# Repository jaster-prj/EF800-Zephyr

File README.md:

# EF800 Zephyr workspace

This repository migrates the EF800 firmware from Mbed OS to Zephyr. Builds run
inside the devcontainer so the Zephyr revision and toolchain do not depend on a
developer's host setup.

The devcontainer follows the `zephyr_gartennode_poolmodul` layout:

```text
/workspace/                         west workspace and build root
/workspace/application/             this Git repository
/workspace/application/application/ firmware applications
/workspace/zephyr/                  downloaded Zephyr checkout
```

The container is intended to be reused during development. `west update` is
not run every time a terminal is opened. Run the initialization commands once
after creating the container; later sessions can build directly.

## Reusable workspace

The development image can already contain a populated west workspace. Inspect
it before running any network operation:

```sh
/opt/venv/bin/west topdir
/opt/venv/bin/west config manifest.path
/opt/venv/bin/west config manifest.file
/opt/venv/bin/west list zephyr -f "{path} {revision} {sha}"
```

If the workspace is `/workspace`, the manifest is
`application/manifest-repo/west.yml`, and Zephyr matches the revision in
`manifest-repo/west.yml`, build directly. Do not run `west update` for normal
development sessions.

Only initialize or update a new, incomplete, or manifest-mismatched container:

```sh
if [ -d .west ]; then
  /opt/venv/bin/west config manifest.path application/manifest-repo
  /opt/venv/bin/west config manifest.file west.yml
else
  /opt/venv/bin/west init -l application/manifest-repo
fi
/opt/venv/bin/west update
/opt/venv/bin/west zephyr-export
/opt/venv/bin/python -m pip install -r zephyr/scripts/requirements.txt
```

Build the six firmware targets with:

```sh
/opt/venv/bin/west build -p always -b ef800 application/application/ef800-application -d application/build/ef800-application
/opt/venv/bin/west build -p always -b ef800 application/application/ef800-backup -d application/build/ef800-backup
/opt/venv/bin/west build -p always -b ef800 application/application/ef800-bootloader -d application/build/ef800-bootloader
/opt/venv/bin/west build -p always -b ef800_keyboard application/application/keyboard-application -d application/build/keyboard-application
/opt/venv/bin/west build -p always -b ef800_keyboard application/application/keyboard-bootloader -d application/build/keyboard-bootloader
/opt/venv/bin/west build -p always -b ef800_keyboard application/application/keyboard-updater -d application/build/keyboard-updater
bash application/scripts/verify-images.sh
```

For the temporary, read-only external-flash hardware-debug image:

```sh
/opt/venv/bin/west build -p always -b ef800 application/application/test-hwdebug -d application/build/test-hwdebug
bash application/scripts/verify-test-hwdebug-image.sh
```

This image replaces the second-level bootloader at `0x08000000` and must only
be used on a recoverable engineering target. It provides a USB CDC diagnostic
console and read-only SPI/QSPI/QPI probing with recovery boundaries; see
`docs/hardware-debug-qspi.md`.

The same commands are collected in `.devcontainer/commands.txt`.

The board definitions are currently kept in this mounted application repository
under `boards/` so the first bring-up does not require a second repository.
They can be moved into a shared Zephyr board module once the hardware has been
verified.

## Current layout

The legacy EF800 internal flash contract is retained for the first migration
increment:

```text
0x08000000 - 0x0800FFFF  second-level bootloader
0x08010000 - 0x0802FFFF  backup application
0x08030000 - 0x080FFFFF  EF800 application
```

The current Zephyr contract reserves `0x08028000..0x0802FFFF` for boot
metadata. The captured legacy `BackupApplication.bin` is 128 KiB and uses that
range, so the reservation must not be treated as unused when restoring the
legacy image. The external QSPI flash is configured as the identified
`IS25LP032D-JTLE-TR` 32-Mbit / 4-MiB device. JEDEC ID, SFDP, signal integrity,
erase geometry, and existing FAT contents still require hardware validation
before production flashing.

The connected STM32L496 engineering target was erased and verified blank during
initial recovery preparation, then later used for controlled bootloader and
EF800 Application bring-up. See `docs/stm32l496-target-snapshot.md` for the
historical option-byte values, recovery-image hashes, and erase record. See
`docs/migration-status.md` for current migration state.

See `docs/` for the migration contract and hardware assumptions.

The system architecture is documented under [`architecture/`](architecture/index.md)
using separately maintained arc42 sections, with block views and runtime
diagrams under `architecture/diagram_as_code/`.

For physical target testing with semantic virtual keyboard input, see
`docs/hardware-debug-keyboard.md`.

For the TLX-711A virtual controller and framebuffer viewer, see
`GSE/TLX-711A/README.md` and build `application/tlx-711a`.

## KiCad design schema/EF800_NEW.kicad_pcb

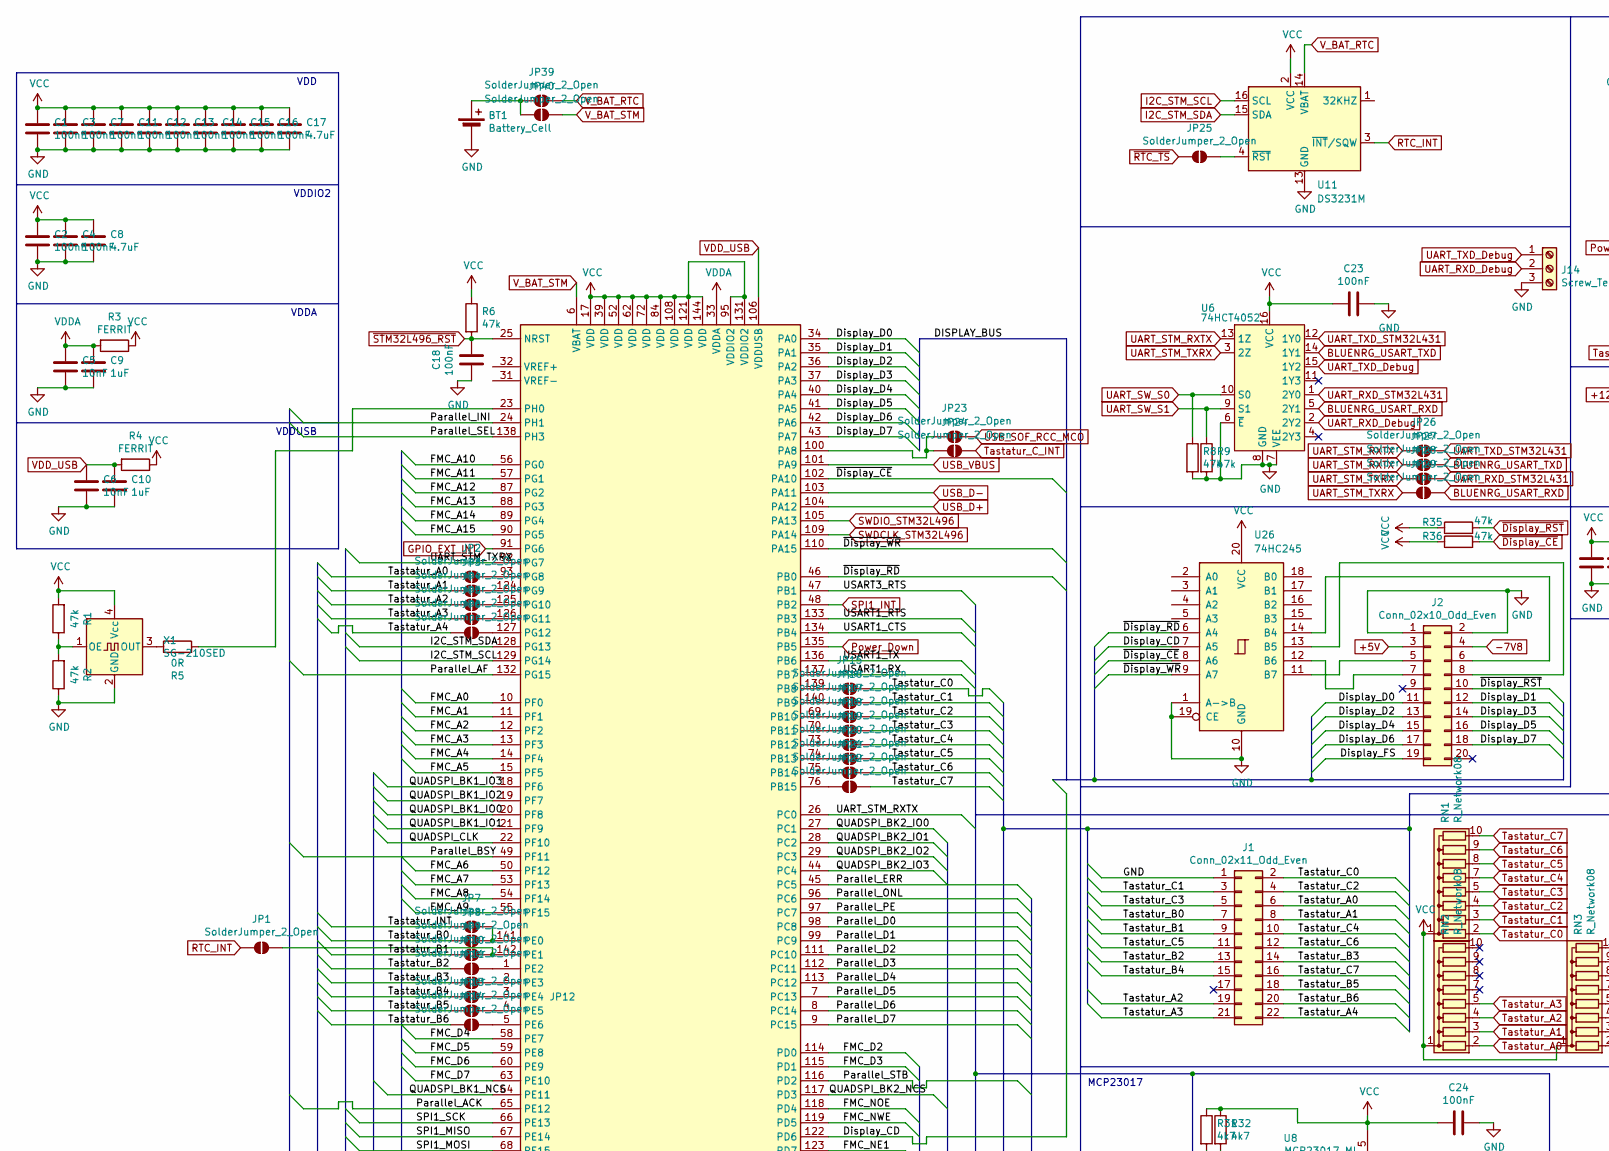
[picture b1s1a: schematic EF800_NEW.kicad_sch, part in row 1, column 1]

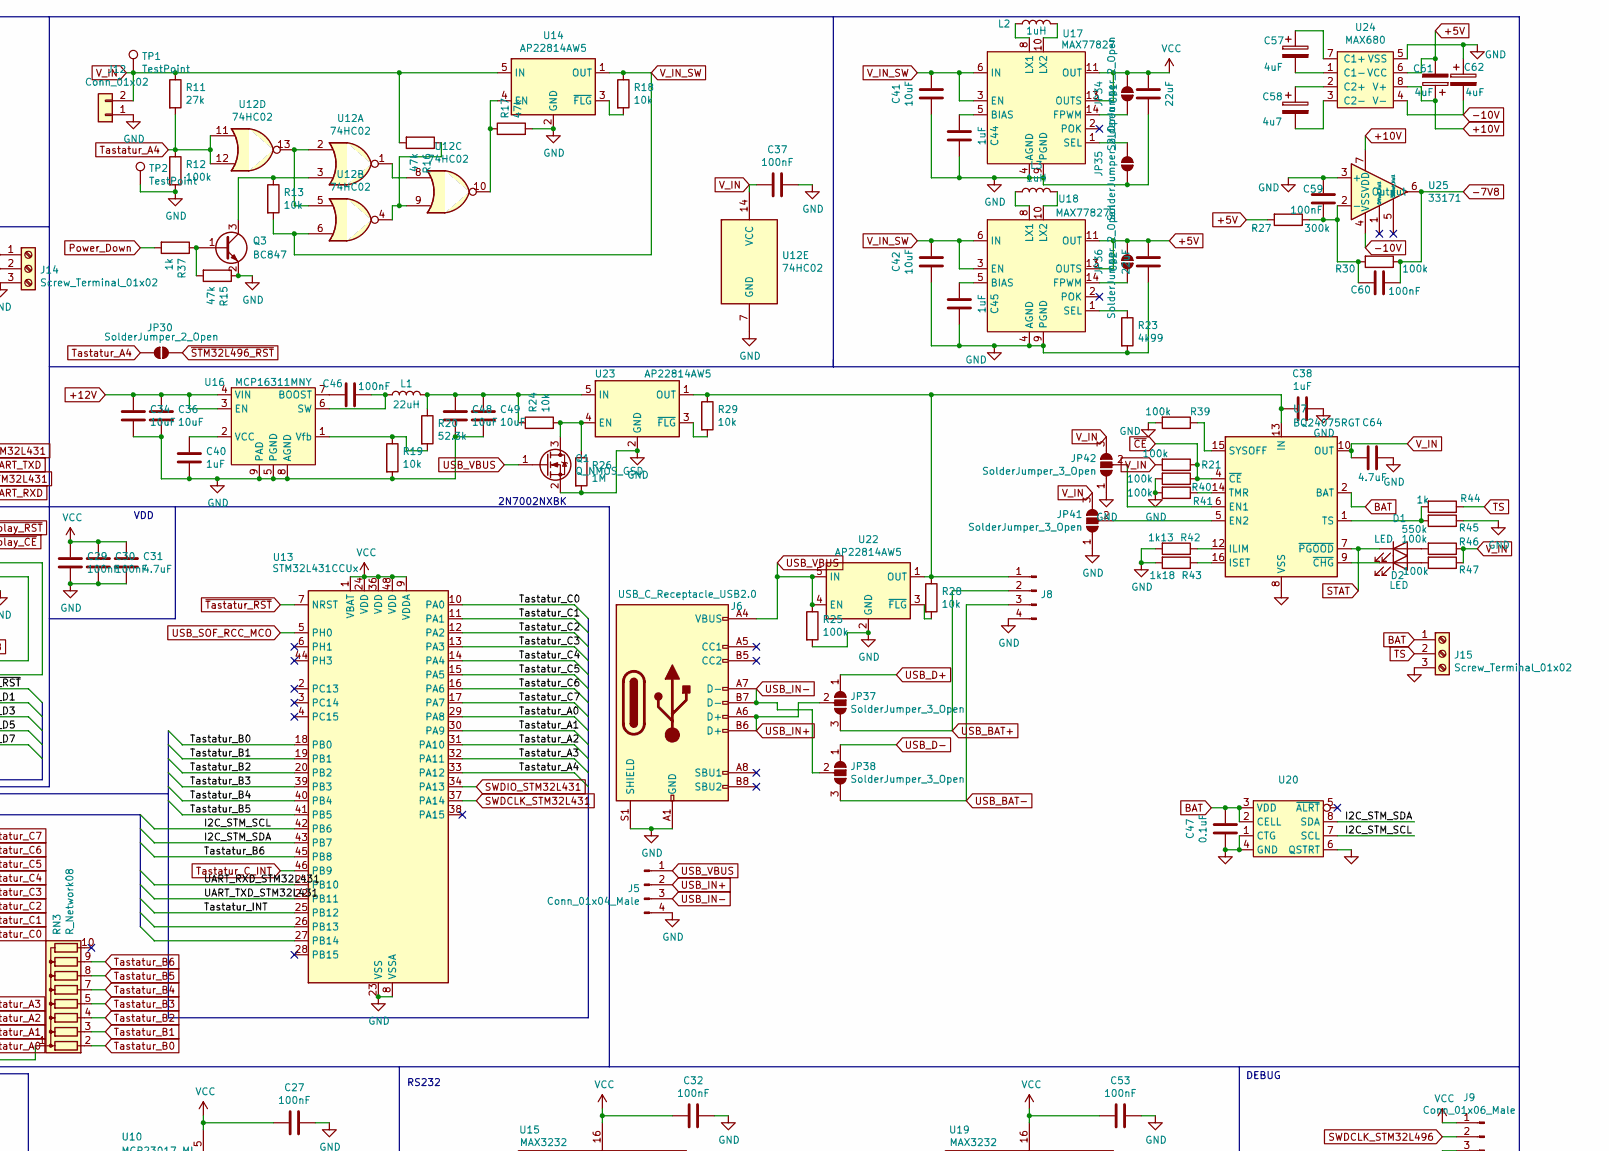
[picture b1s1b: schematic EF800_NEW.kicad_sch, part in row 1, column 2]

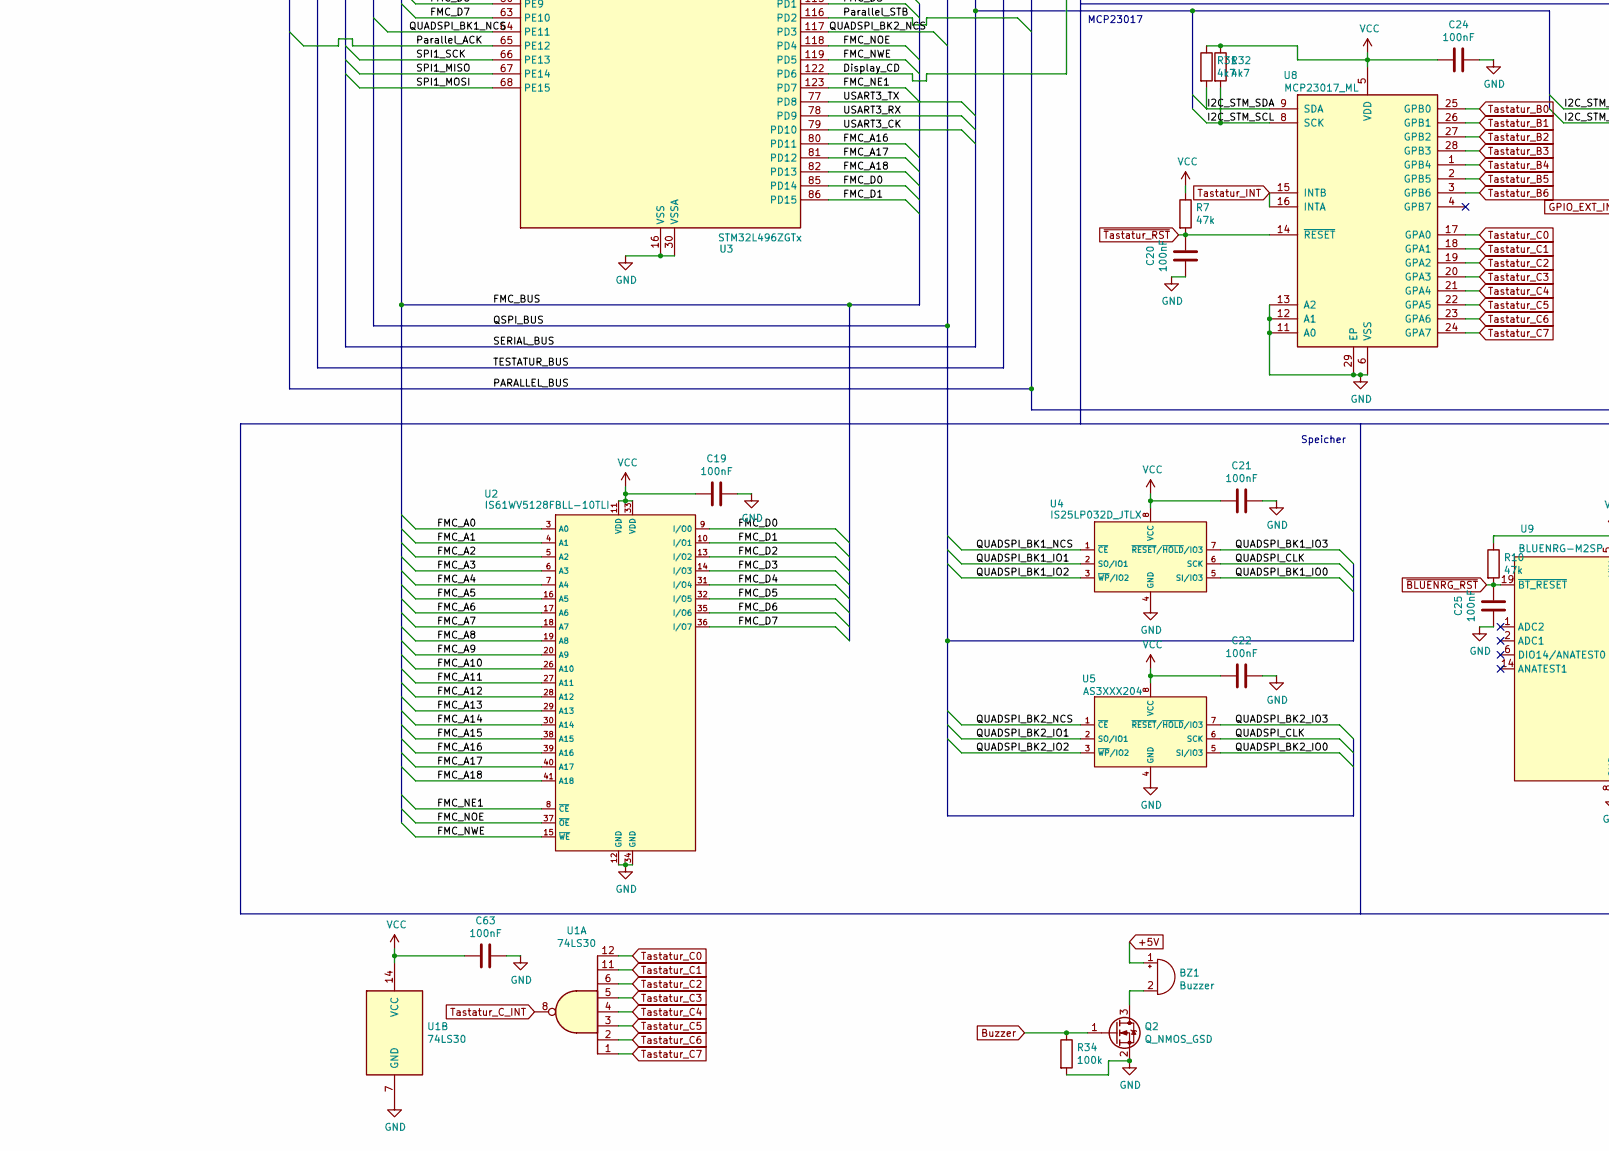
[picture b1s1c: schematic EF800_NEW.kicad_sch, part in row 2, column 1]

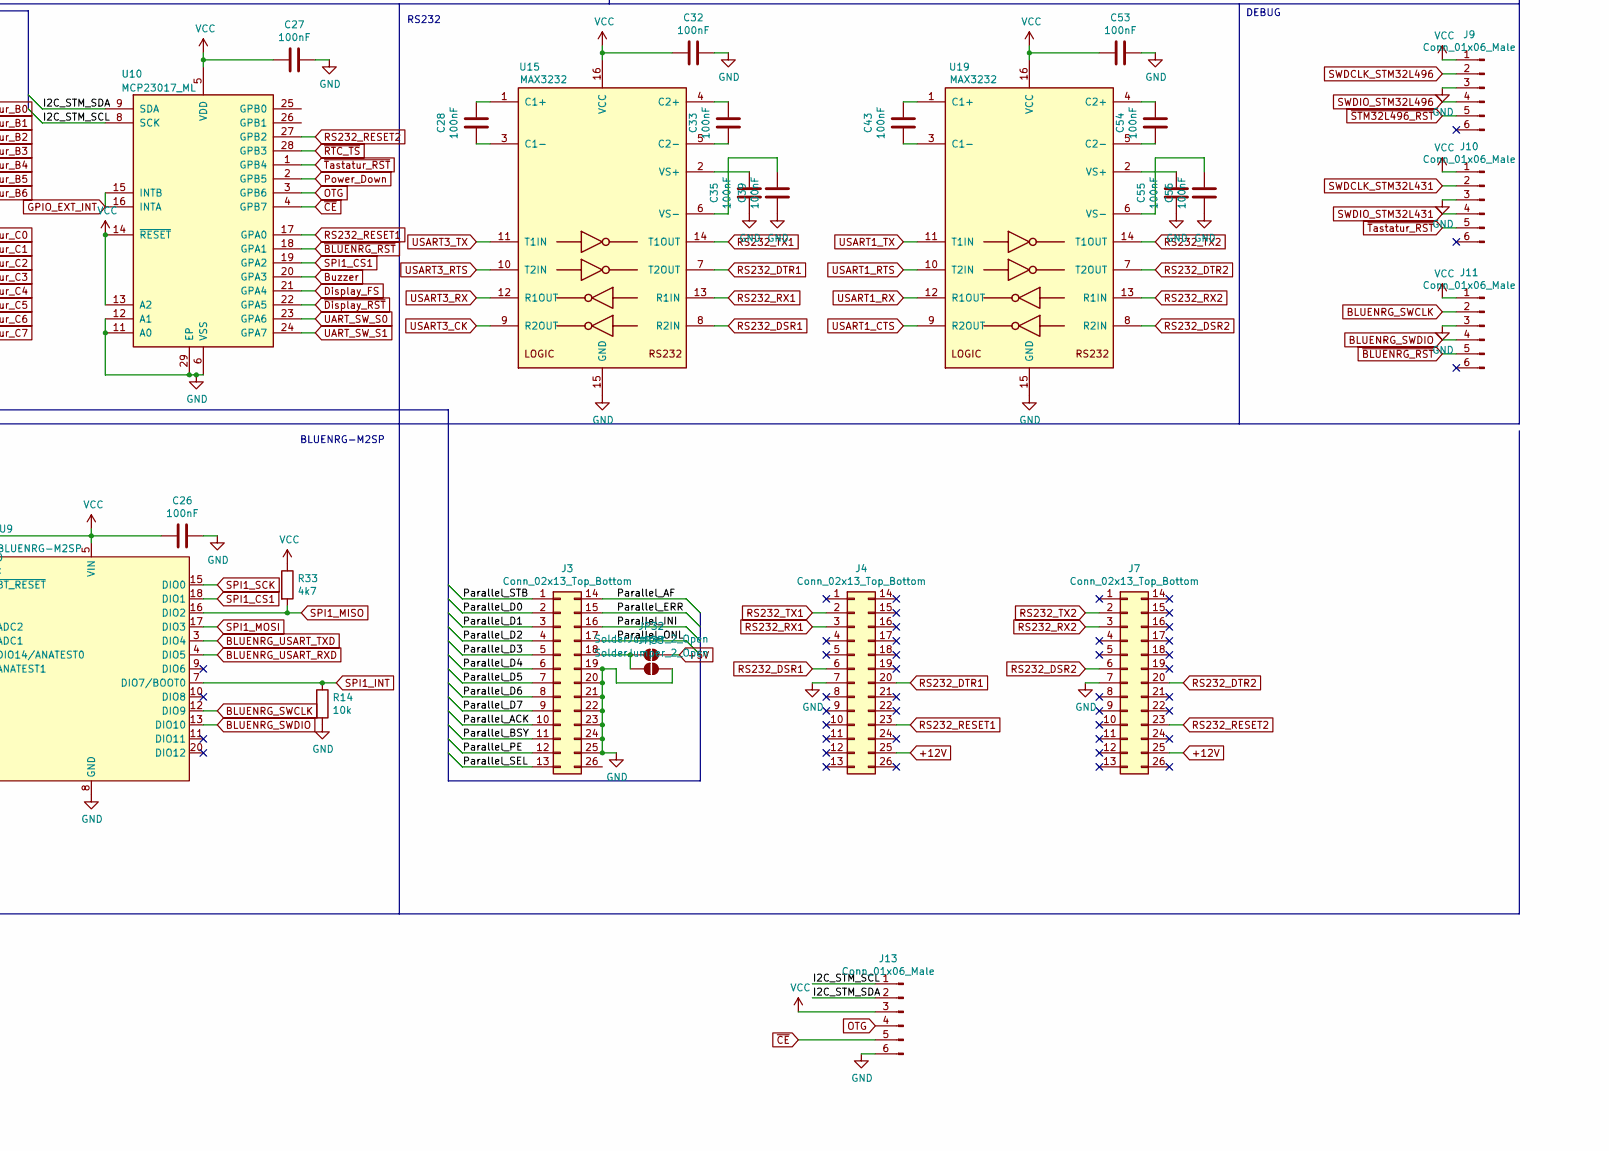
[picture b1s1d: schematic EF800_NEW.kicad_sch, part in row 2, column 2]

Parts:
BT1: Battery_Cell; BatteryHolder_Keystone_1057_1x2032
BZ1: Buzzer; Buzzer_12x9.5RM7.6
C1, C2, C3, C4, C7, C11, C12, C13, C14, C15, C16, C18, C19, C20, C21, C22, C23, C24, C25, C26, C27, C28, C29, C30, C32, C33, C35, C37, C39, C43, C46, C53, C54, C55, C56, C59, C60, C63: 100nF; C_0402_1005Metric
C5, C6: 10nF; C_0402_1005Metric
C8, C17, C31: 4.7uF; C_0603_1608Metric
C9, C10, C38, C40, C44, C45: 1uF; C_0402_1005Metric
C34, C36, C41, C42, C48, C49: 10uF; C_0603_1608Metric
C47: 0.1uF; C_0402_1005Metric
C51, C52: 22uF; C_0603_1608Metric
C57, C61, C62: 4uF; C_0603_1608Metric
C58: 4u7; C_0603_1608Metric
C64: 4.7uF; C_0805_2012Metric
D1, D2: LED; LED_0402_1005Metric
J1: Conn_02x11_Odd_Even; PinSocket_2x11_P2.54mm_Vertical
J2: Conn_02x10_Odd_Even; PinSocket_2x10_P2.54mm_Vertical
J3, J4, J7: Conn_02x13_Top_Bottom; PinSocket_2x13_P2.54mm_Vertical_Top_Buttom
J5, J8: Conn_01x04_Male; JST_GH_SM04B-GHS-TB_1x04-1MP_P1.25mm_Horizontal
J6: USB_C_Receptacle_USB2.0; USB_C_Receptacle_JAE_DX07S016JA1
J9, J10, J11, J13: Conn_01x06_Male; JST_GH_SM06B-GHS-TB_1x06-1MP_P1.25mm_Horizontal
J12: Conn_01x02; TerminalBlock_bornier-2_P5.08mm
J14, J15: Screw_Terminal_01x02; PinSocket_1x03_P2.54mm_Vertical
JP1, JP2, JP3, JP4, JP5, JP6, JP7, JP8, JP9, JP10, JP11, JP12, JP13, JP14, JP15, JP16, JP17, JP18, JP19, JP20, JP21, JP22, JP23, JP24, JP25, JP26, JP27, JP28, JP29, JP30, JP32, JP33, JP34, JP35, JP36, JP39, JP40: SolderJumper_2_Open; SolderJumper-2_0805_Open
JP37, JP38, JP41, JP42: SolderJumper_3_Open; SolderJumper-3_P0,7mm_Open_Pad0.5x0.5mm
L1: 22uH; L_Wuerth_WE-PD-Typ-M-Typ-S
L2, L3: 1uH; L_0805_2012Metric
Q1, Q2: Q_NMOS_GSD; SOT-23
Q3: BC847; SOT-23
R1, R2, R6, R7, R8, R9, R10, R15, R16, R17, R35, R36: 47k; R_0402_1005Metric
R3, R4: FERRIT; R_0603_1608Metric
R5: 0R; R_0402_1005Metric
R11: 27k; R_0402_1005Metric
R12, R21, R25, R30, R34, R39, R40, R41, R46, R47: 100k; R_0402_1005Metric
R13, R14, R18, R19, R24, R28, R29: 10k; R_0402_1005Metric
R20: 52.3k; R_0402_1005Metric
R23: 4k99; R_0402_1005Metric
R26: 1M; R_0402_1005Metric
R27: 300k; R_0402_1005Metric
R31, R32, R33: 4k7; R_0402_1005Metric
R37, R44: 1k; R_0402_1005Metric
R42: 1k13; R_0402_1005Metric
R43: 1k18; R_0402_1005Metric
R45: 550k; R_0402_1005Metric
RN1, RN2, RN3: R_Network08; R_Array_EXBD
TP1, TP2: TestPoint; TestPoint_THTPad_3.0x3.0mm_Drill1.5mm
U1: 74LS30; SOIC-14_3.9x8.7mm_P1.27mm
U2: IS61WV5128FBLL-10TLI; TSOP-II-44_10.16x18.41mm_P0.8mm
U3: STM32L496ZGTx; LQFP-144_20x20mm_P0.5mm
U4: IS25LP032D_JTLX; USON-8_4x3mm_P0.8mm
U5: AS3XXX204; WSON-8-1EP_6x5mm_P1.27mm_EP3.4x4mm
U6: 74HCT4052; DHVQFN-16-1EP_3.5x2.5mm_P0.5mm_EP2x1mm_ThermalVias
U7: BQ24075RGT; VQFN-16-1EP_3x3mm_P0.5mm_EP1.6x1.6mm
U8, U10: MCP23017_ML; QFN-28-1EP_6x6mm_P0.65mm_EP4.25x4.25mm
U9: BLUENRG-M2SP; BLUENRG_M2SP
U11: DS3231M; SOIC-16W_7.5x10.3mm_P1.27mm
U12: 74HC02; DHVQFN-14-1EP_3x2.5mm_P0.5mm_EP1.5x1mm_ThermalVias
U13: STM32L431CCUx; QFN-48-1EP_7x7mm_P0.5mm_EP5.6x5.6mm
U14, U22, U23: AP22814AW5; SOT-23-5
U15, U19: MAX3232; SOIC-16_3.9x9.9mm_P1.27mm
U16: MCP16311MNY; DFN-8-1EP_3x2mm_P0.5mm_EP1.75x1.45mm
U17, U18: MAX77827; Maxim_FC2QFN-14_2.5x2.5_P0.55mm
U20: TDFN-8-1EP_2x2mm_P0.5mm_EP0.8x1.2mm
U24: MAX680; SOIC-8_3.9x4.9mm_P1.27mm
U25: 33171; SOIC-8_3.9x4.9mm_P1.27mm
U26: 74HC245; SOIC-20W_7.5x12.8mm_P1.27mm
X1: SG-210SED; Oscillator_SMD_SeikoEpson_SG210-4Pin_2.5x2.0mm

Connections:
+5V: BZ1.1 (+), C52.1, C61.2, J2.3, JP32.2 (B), JP36.2 (B), R27.2, U18.11 (OUT), U18.13 (OUTS), U24.6 (VCC)
+10V: C61.1, U24.8 (V+), U25.7 (VDD)
+12V: C34.1, C36.1, J4.25, J7.25, U16.3 (EN), U16.4 (VIN)
-7V8: C60.2, J2.4, R30.1, U25.6 (Output)
-10V: C62.2, U24.4 (V-), U25.4 (VSS)
/Display_CD: U3.122 (PD6), U26.7 (A5)
/Display_D0: J2.11, U3.34 (PA0)
/Display_D1: J2.12, U3.35 (PA1)
/Display_D2: J2.13, U3.36 (PA2)
/Display_D3: J2.14, U3.37 (PA3)
/Display_D4: J2.15, U3.40 (PA4)
/Display_D5: J2.16, U3.41 (PA5)
/Display_D6: J2.17, U3.42 (PA6)
/Display_D7: J2.18, U3.43 (PA7)
/FMC_A0: U2.3 (A0), U3.10 (PF0)
/FMC_A1: U2.4 (A1), U3.11 (PF1)
/FMC_A2: U2.5 (A2), U3.12 (PF2)
/FMC_A3: U2.6 (A3), U3.13 (PF3)
/FMC_A4: U2.7 (A4), U3.14 (PF4)
/FMC_A5: U2.16 (A5), U3.15 (PF5)
/FMC_A6: U2.17 (A6), U3.50 (PF12)
/FMC_A7: U2.18 (A7), U3.53 (PF13)
/FMC_A8: U2.19 (A8), U3.54 (PF14)
/FMC_A9: U2.20 (A9), U3.55 (PF15)
/FMC_A10: U2.26 (A10), U3.56 (PG0)
/FMC_A11: U2.27 (A11), U3.57 (PG1)
/FMC_A12: U2.28 (A12), U3.87 (PG2)
/FMC_A13: U2.29 (A13), U3.88 (PG3)
/FMC_A14: U2.30 (A14), U3.89 (PG4)
/FMC_A15: U2.38 (A15), U3.90 (PG5)
/FMC_A16: U2.39 (A16), U3.80 (PD11)
/FMC_A17: U2.40 (A17), U3.81 (PD12)
/FMC_A18: U2.41 (A18), U3.82 (PD13)
/FMC_D0: U2.9 (I/O0), U3.85 (PD14)
/FMC_D1: U2.10 (I/O1), U3.86 (PD15)
/FMC_D2: U2.13 (I/O2), U3.114 (PD0)
/FMC_D3: U2.14 (I/O3), U3.115 (PD1)
/FMC_D4: U2.31 (I/O4), U3.58 (PE7)
/FMC_D5: U2.32 (I/O5), U3.59 (PE8)
/FMC_D6: U2.35 (I/O6), U3.60 (PE9)
/FMC_D7: U2.36 (I/O7), U3.63 (PE10)
/FMC_NE1: U2.8 (~CE), U3.123 (PD7)
/FMC_NOE: U2.37 (~OE), U3.118 (PD4)
/FMC_NWE: U2.15 (~WE), U3.119 (PD5)
/Parallel_ACK: J3.10, U3.65 (PE12)
/Parallel_AF: J3.14, U3.132 (PG15)
/Parallel_BSY: J3.11, U3.49 (PF11)
/Parallel_D0: J3.2, U3.98 (PC8)
/Parallel_D1: J3.3, U3.99 (PC9)
/Parallel_D2: J3.4, U3.111 (PC10)
/Parallel_D3: J3.5, U3.112 (PC11)
/Parallel_D4: J3.6, U3.113 (PC12)
/Parallel_D5: J3.7, U3.7 (PC13)
/Parallel_D6: J3.8, U3.8 (PC14)
/Parallel_D7: J3.9, U3.9 (PC15)
/Parallel_ERR: J3.15, U3.45 (PC5)
/Parallel_INI: J3.16, U3.24 (PH1)
/Parallel_ONL: J3.17, U3.96 (PC6)
/Parallel_PE: J3.12, U3.97 (PC7)
/Parallel_SEL: J3.13, U3.138 (PH3)
/Parallel_STB: J3.1, U3.116 (PD2)
/QUADSPI_BK1_IO0: U3.20 (PF8), U4.5 (SI/IO3)
/QUADSPI_BK1_IO1: U3.21 (PF9), U4.2 (SO/IO1)
/QUADSPI_BK1_IO2: U3.19 (PF7), U4.3 (~WP/IO2)
/QUADSPI_BK1_IO3: U3.18 (PF6), U4.7 (~RESET/~HOLD/IO3)
/QUADSPI_BK1_NCS: U3.64 (PE11), U4.1 (~CE)
/QUADSPI_BK2_IO0: U3.27 (PC1), U5.5 (SI/IO3)
/QUADSPI_BK2_IO1: U3.28 (PC2), U5.2 (SO/IO1)
/QUADSPI_BK2_IO2: U3.29 (PC3), U5.3 (~WP/IO2)
/QUADSPI_BK2_IO3: U3.44 (PC4), U5.7 (~RESET/~HOLD/IO3)
/QUADSPI_BK2_NCS: U3.117 (PD3), U5.1 (~CE)
/QUADSPI_CLK: U3.22 (PF10), U4.6 (SCK), U5.6 (SCK)
/~Display_RD: U3.46 (PB0), U26.6 (A4)
/~Display_WR: U3.110 (PA15), U26.9 (A7)
BAT: C47.1, J15.1, U7.2 (BAT), U7.3 (BAT), U20.2 (CELL), U20.3 (VDD)
BLUENRG_SWCLK: J11.2, U9.12 (DIO9)
BLUENRG_SWDIO: J11.4, U9.13 (DIO10)
BLUENRG_USART_RXD: JP29.2 (B), U6.5 (2Y1), U9.4 (DIO5)
BLUENRG_USART_TXD: JP27.2 (B), U6.14 (1Y1), U9.3 (DIO4)
Buzzer: Q2.1 (G), R34.1, U10.20 (GPA3)
Display_FS: J2.19, U10.21 (GPA4)
GND: BT1.2 (-), C1.1, C2.1, C3.1, C4.1, C5.1, C6.1, C7.1, C8.1, C9.1, C10.1, C11.1, C12.1, C13.1, C14.1, C15.1, C16.1, C17.1, C18.2, C19.1, C20.2, C21.1, C22.1, C23.1, C24.1, C25.2, C26.1, C27.1, C29.1, C30.1, C31.1, C32.1, C34.2, C35.2, C36.2, C37.1, C38.1, C39.2, C40.2, C41.2, C42.2, C44.1, C45.1, C47.2, C48.2, C49.2, C51.2, C52.2, C53.1, C55.2, C56.2, C59.2, C62.1, C63.1, C64.1, J1.1, J2.1, J2.2, J3.19, J3.20, J3.21, J3.22, J3.23, J3.24, J3.25, J4.7, J5.4, J6.A1 (GND), J6.A12 (GND), J6.B1 (GND), J6.B12 (GND), J6.S1 (SHIELD), J7.7, J8.4, J9.3, J10.3, J11.3, J12.1, J13.6, J14.3, J15.3, JP33.2 (B), JP35.1 (A), JP41.1 (A), JP42.1 (A), Q1.2 (S), Q2.2 (S), Q3.2 (E), R2.1, R8.2, R9.2, R12.2, R14.2, R15.1, R17.2, R19.2, R23.2, R25.2, R26.2, R34.2, R39.2, R40.2, R41.2, R42.2, R43.2, R45.1, TP2.1, U1.7 (GND), U2.12 (GND), U2.34 (GND), U3.16 (VSS), U3.30 (VSSA), U3.38 (VSS), U3.51 (VSS), U3.61 (VSS), U3.71 (VSS), U3.83 (VSS), U3.94 (VSS), U3.107 (VSS), U3.120 (VSS), U3.130 (VSS), U3.143 (VSS), U4.4 (GND), U5.4 (GND), U6.6 (~E), U6.7 (VEE), U6.8 (GND), U6.17 (PAD), U7.8 (VSS), U7.17 (VSS), U8.6 (VSS), U8.11 (A0), U8.12 (A1), U8.13 (A2), U8.29 (EP), U9.8 (GND), U10.6 (VSS), U10.11 (A0), U10.12 (A1), U10.29 (EP), U11.5 (GND), U11.6 (GND), U11.7 (GND), U11.8 (GND), U11.9 (GND), U11.10 (GND), U11.11 (GND), U11.12 (GND), U11.13 (GND), U12.7 (GND), U13.8 (VSSA), U13.23 (VSS), U13.35 (VSS), U13.47 (VSS), U13.49 (VSS), U14.2 (GND), U15.15 (GND), U16.5 (PGND), U16.8 (AGND), U16.9 (PAD), U17.4 (AGND), U17.9 (PGND), U18.4 (AGND), U18.9 (PGND), U19.15 (GND), U20.1 (CTG), U20.4 (GND), U20.6 (QSTRT), U20.9 (PAD), U22.2 (GND), U23.2 (GND), U24.5 (VSS), U25.3 (+), U26.1 (A->B), U26.10 (GND), U26.19 (CE), X1.2 (GND)
GPIO_EXT_INT: U3.91 (PG6), U10.15 (INTB), U10.16 (INTA)
I2C_STM_SCL: J13.1, R32.2, U3.129 (PG14), U8.8 (SCK), U10.8 (SCK), U11.16 (SCL), U13.42 (PB6), U20.7 (SCL)
I2C_STM_SDA: J13.2, R31.2, U3.128 (PG13), U8.9 (SDA), U10.9 (SDA), U11.15 (SDA), U13.43 (PB7), U20.8 (SDA)
unnamed: BT1.1 (+), JP39.1 (A), JP40.1 (A)
unnamed: BZ1.2 (-), Q2.3 (D)
unnamed: D1.2 (A), R46.2
unnamed: D2.2 (A), R47.2
unnamed: D2.1 (K), U7.9 (~CHG)
unnamed: J2.5, U26.11 (B7)
unnamed: J2.6, U26.14 (B4)
unnamed: J2.7, U26.12 (B6)
unnamed: J2.8, U26.13 (B5)
unnamed: J3.18, JP32.1 (A), JP33.1 (A)
unnamed: C38.2, J8.1, R28.1, R29.1, U7.13 (IN), U22.1 (OUT), U23.1 (OUT)
unnamed: JP1.2 (B), JP9.2 (B), U3.142 (PE1)
unnamed: JP2.2 (B), U3.93 (PG8)
unnamed: JP3.2 (B), U3.124 (PG9)
unnamed: JP4.2 (B), U3.125 (PG10)
unnamed: JP5.2 (B), U3.126 (PG11)
unnamed: JP6.2 (B), U3.127 (PG12)
unnamed: JP7.2 (B), JP8.2 (B), U3.141 (PE0)
unnamed: JP10.2 (B), U3.1 (PE2)
unnamed: JP11.2 (B), U3.2 (PE3)
unnamed: JP12.2 (B), U3.3 (PE4)
unnamed: JP13.2 (B), U3.4 (PE5)
unnamed: JP14.2 (B), U3.5 (PE6)
unnamed: JP15.1 (A), U3.139 (PB8)
unnamed: JP16.1 (A), U3.140 (PB9)
unnamed: JP17.1 (A), U3.69 (PB10)
unnamed: JP18.1 (A), U3.70 (PB11)
unnamed: JP19.1 (A), U3.73 (PB12)
unnamed: JP20.1 (A), U3.74 (PB13)
unnamed: JP21.1 (A), U3.75 (PB14)
unnamed: JP22.1 (A), U3.76 (PB15)
unnamed: JP23.1 (A), JP24.1 (A), U3.100 (PA8)
unnamed: JP25.2 (B), U11.4 (~RST)
unnamed: JP34.1 (A), U17.14 (FPWM)
unnamed: JP35.2 (B), U17.1 (SEL)
unnamed: JP36.1 (A), U18.14 (FPWM)
unnamed: JP41.2 (C), U7.5 (EN2)
unnamed: JP42.2 (C), U7.6 (EN1)
unnamed: Q1.3 (D), R24.2, R26.1, U23.4 (EN)
unnamed: Q3.1 (B), R15.2, R37.1
unnamed: Q3.3 (C), R13.1, U12.3
unnamed: R16.1, U12.4, U12.9
unnamed: R5.2, U3.23 (PH0)
unnamed: R42.1, U7.12 (ILIM)
unnamed: R43.1, U7.16 (ISET)
unnamed: R39.1, U7.15 (SYSOFF)
unnamed: R41.1, U7.14 (TMR)
unnamed: R44.2, R45.2, U7.1 (TS)
unnamed: U12.1, U12.8
unnamed: U12.2, U12.5, U12.13
unnamed: R17.1, U12.10, U14.4 (EN)
unnamed: R18.2, U14.3 (~FLG)
unnamed: C28.1, U15.1 (C1+)
unnamed: C28.2, U15.3 (C1-)
unnamed: C33.1, U15.4 (C2+)
unnamed: C33.2, U15.5 (C2-)
unnamed: C35.1, U15.2 (VS+)
unnamed: C39.1, U15.6 (VS-)
unnamed: C46.1, U16.7 (BOOST)
unnamed: C46.2, L1.1, U16.6 (SW)
unnamed: C40.1, U16.2 (VCC)
unnamed: R19.1, R20.2, U16.1 (Vfb)
unnamed: C44.2, U17.5 (BIAS)
unnamed: L2.1, U17.8 (LX1)
unnamed: L2.2, U17.10 (LX2)
unnamed: C45.2, U18.5 (BIAS)
unnamed: L3.1, U18.8 (LX1)
unnamed: L3.2, U18.10 (LX2)
unnamed: R23.1, U18.1 (SEL)
unnamed: C43.1, U19.1 (C1+)
unnamed: C43.2, U19.3 (C1-)
unnamed: C54.1, U19.4 (C2+)
unnamed: C54.2, U19.5 (C2-)
unnamed: C55.1, U19.2 (VS+)
unnamed: C56.1, U19.6 (VS-)
unnamed: R28.2, U22.3 (~FLG)
unnamed: C48.1, C49.1, L1.2, R20.1, R24.1, U23.5 (IN)
unnamed: R29.2, U23.3 (~FLG)
unnamed: C57.1, U24.7 (C1+)
unnamed: C57.2, U24.1 (C1-)
unnamed: C58.1, U24.2 (C2+)
unnamed: C58.2, U24.3 (C2-)
unnamed: C59.1, C60.1, R27.1, R30.2, U25.2 (-)
unnamed: R1.1, R2.2, X1.1 (OE)
unnamed: R5.1, X1.3 (OUT)
OTG: J13.4, U10.3 (GPB6)
Power_Down: R37.2, U3.135 (PB5), U10.2 (GPB5)
RS232_DSR1: J4.6, U15.8 (R2IN)
RS232_DSR2: J7.6, U19.8 (R2IN)
RS232_DTR1: J4.20, U15.7 (T2OUT)
RS232_DTR2: J7.20, U19.7 (T2OUT)
RS232_RESET1: J4.23, U10.17 (GPA0)
RS232_RESET2: J7.23, U10.27 (GPB2)
RS232_RX1: J4.3, U15.13 (R1IN)
RS232_RX2: J7.3, U19.13 (R1IN)
RS232_TX1: J4.2, U15.14 (T1OUT)
RS232_TX2: J7.2, U19.14 (T1OUT)
RTC_INT: JP1.1 (A), U11.3 (~INT/SQW)
SPI1_CS1: U9.18 (DIO1), U10.19 (GPA2)
SPI1_INT: R14.1, U3.48 (PB2), U9.7 (DIO7/BOOT0)
SPI1_MISO: R33.2, U3.67 (PE14), U9.16 (DIO2)
SPI1_MOSI: U3.68 (PE15), U9.17 (DIO3)
SPI1_SCK: U3.66 (PE13), U9.15 (DIO0)
STAT: D1.1 (K), U7.7 (~PGOOD)
SWDCLK_STM32L431: J10.2, U13.37 (PA14)
SWDCLK_STM32L496: J9.2, U3.109 (PA14)
SWDIO_STM32L431: J10.4, U13.34 (PA13)
SWDIO_STM32L496: J9.4, U3.105 (PA13)
TS: J15.2, R44.1
Tastatur_A0: J1.6, JP2.1 (A), RN2.2 (R1), U13.29 (PA8)
Tastatur_A1: J1.8, JP3.1 (A), RN2.3 (R2), U13.30 (PA9)
Tastatur_A2: J1.19, JP4.1 (A), RN2.4 (R3), U13.31 (PA10)
Tastatur_A3: J1.21, JP5.1 (A), RN2.5 (R4), U13.32 (PA11)
Tastatur_A4: J1.22, JP6.1 (A), JP30.1 (A), R11.2, R12.1, U12.11, U12.12, U13.33 (PA12)
Tastatur_B0: J1.7, JP8.1 (A), RN3.2 (R1), U8.25 (GPB0), U13.18 (PB0)
Tastatur_B1: J1.9, JP9.1 (A), RN3.3 (R2), U8.26 (GPB1), U13.19 (PB1)
Tastatur_B2: J1.13, JP10.1 (A), RN3.4 (R3), U8.27 (GPB2), U13.20 (PB2)
Tastatur_B3: J1.14, JP11.1 (A), RN3.5 (R4), U8.28 (GPB3), U13.39 (PB3)
Tastatur_B4: J1.15, JP12.1 (A), RN3.7 (R5), U8.1 (GPB4), U13.40 (PB4)
Tastatur_B5: J1.18, JP13.1 (A), RN3.8 (R6), U8.2 (GPB5), U13.41 (PB5)
Tastatur_B6: J1.20, JP14.1 (A), RN3.9 (R7), U8.3 (GPB6), U13.45 (PB8)
Tastatur_C0: J1.2, JP15.2 (B), RN1.2 (R1), U1.12, U8.17 (GPA0), U13.10 (PA0)
Tastatur_C1: J1.3, JP16.2 (B), RN1.3 (R2), U1.11, U8.18 (GPA1), U13.11 (PA1)
Tastatur_C2: J1.4, JP17.2 (B), RN1.4 (R3), U1.6, U8.19 (GPA2), U13.12 (PA2)
Tastatur_C3: J1.5, JP18.2 (B), RN1.5 (R4), U1.5, U8.20 (GPA3), U13.13 (PA3)
Tastatur_C4: J1.10, JP19.2 (B), RN1.7 (R5), U1.4, U8.21 (GPA4), U13.14 (PA4)
Tastatur_C5: J1.11, JP20.2 (B), RN1.8 (R6), U1.3, U8.22 (GPA5), U13.15 (PA5)
Tastatur_C6: J1.12, JP21.2 (B), RN1.9 (R7), U1.2, U8.23 (GPA6), U13.16 (PA6)
Tastatur_C7: J1.16, JP22.2 (B), RN1.10 (R8), U1.1, U8.24 (GPA7), U13.17 (PA7)
Tastatur_C_INT: JP24.2 (B), U1.8, U13.46 (PB9)
Tastatur_INT: JP7.1 (A), U8.15 (INTB), U8.16 (INTA), U13.25 (PB12)
UART_RXD_Debug: J14.2, U6.2 (2Y2)
UART_RXD_STM32L431: JP28.2 (B), U6.1 (2Y0), U13.21 (PB10)
UART_STM_RXTX: JP26.1 (A), JP27.1 (A), U3.26 (PC0), U6.13 (1Z)
UART_STM_TXRX: JP28.1 (A), JP29.1 (A), U3.92 (PG7), U6.3 (2Z)
UART_SW_S0: R8.1, U6.10 (S0), U10.23 (GPA6)
UART_SW_S1: R9.1, U6.9 (S1), U10.24 (GPA7)
UART_TXD_Debug: J14.1, U6.15 (1Y2)
UART_TXD_STM32L431: JP26.2 (B), U6.12 (1Y0), U13.22 (PB11)
USART1_CTS: U3.134 (PB4), U19.9 (R2OUT)
USART1_RTS: U3.133 (PB3), U19.10 (T2IN)
USART1_RX: U3.137 (PB7), U19.12 (R1OUT)
USART1_TX: U3.136 (PB6), U19.11 (T1IN)
USART3_CK: U3.79 (PD10), U15.9 (R2OUT)
USART3_RTS: U3.47 (PB1), U15.10 (T2IN)
USART3_RX: U3.78 (PD9), U15.12 (R1OUT)
USART3_TX: U3.77 (PD8), U15.11 (T1IN)
USB_BAT+: J8.2, JP37.3 (B)
USB_BAT-: J8.3, JP38.3 (B)
USB_D+: JP37.1 (A), U3.104 (PA12)
USB_D-: JP38.1 (A), U3.103 (PA11)
USB_IN+: J5.2, J6.A6 (D+), J6.B6 (D+), JP37.2 (C)
USB_IN-: J5.3, J6.A7 (D-), J6.B7 (D-), JP38.2 (C)
USB_SOF_RCC_MCO: JP23.2 (B), U13.5 (PH0)
USB_VBUS: J5.1, J6.A4 (VBUS), J6.A9 (VBUS), J6.B4 (VBUS), J6.B9 (VBUS), Q1.1 (G), R25.1, U3.101 (PA9), U22.4 (EN), U22.5 (IN)
VCC: C1.2, C2.2, C3.2, C4.2, C7.2, C8.2, C11.2, C12.2, C13.2, C14.2, C15.2, C16.2, C17.2, C19.2, C21.2, C22.2, C23.2, C24.2, C26.2, C27.2, C29.2, C30.2, C31.2, C32.2, C51.1, C53.2, C63.2, J9.1, J10.1, J11.1, J13.3, JP34.2 (B), R1.2, R3.1, R4.1, R6.1, R7.1, R10.1, R31.1, R32.1, R33.1, R35.1, R36.1, RN1.1 (common), RN1.6 (common), RN2.1 (common), RN2.6 (common), RN3.1 (common), RN3.6 (common), U1.14 (VCC), U2.11 (VDD), U2.33 (VDD), U3.17 (VDD), U3.39 (VDD), U3.52 (VDD), U3.62 (VDD), U3.72 (VDD), U3.84 (VDD), U3.95 (VDDIO2), U3.108 (VDD), U3.121 (VDD), U3.131 (VDDIO2), U3.144 (VDD), U4.8 (VCC), U5.8 (VCC), U6.16 (VCC), U8.5 (VDD), U9.5 (VIN), U10.5 (VDD), U10.13 (A2), U10.14 (~RESET), U11.2 (VCC), U13.1 (VBAT), U13.9 (VDDA), U13.24 (VDD), U13.36 (VDD), U13.48 (VDD), U15.16 (VCC), U17.11 (OUT), U17.13 (OUTS), U19.16 (VCC), U26.20 (VCC), X1.4 (Vcc)
VDDA: C5.2, C9.2, R3.2, U3.33 (VDDA)
VDD_USB: C6.2, C10.2, R4.2, U3.106 (VDDUSB)
V_BAT_RTC: JP39.2 (B), U11.14 (VBAT)
V_BAT_STM: JP40.2 (B), U3.6 (VBAT)
V_IN: C37.2, C64.2, J12.2, JP41.3 (B), JP42.3 (B), R11.1, R16.2, R21.2, R46.1, R47.1, TP1.1, U7.10 (OUT), U7.11 (OUT), U12.14 (VCC), U14.5 (IN)
V_IN_SW: C41.1, C42.1, R13.2, R18.1, U12.6, U14.1 (OUT), U17.3 (EN), U17.6 (IN), U18.3 (EN), U18.6 (IN)
~BLUENRG_RST: C25.1, J11.5, R10.2, U9.19 (~BT_RESET), U10.18 (GPA1)
~CE: J13.5, R21.1, R40.1, U7.4 (~CE), U10.4 (GPB7)
~Display_CE: R36.2, U3.102 (PA10), U26.8 (A6)
~Display_RST: J2.10, R35.2, U10.22 (GPA5)
~RTC_TS: JP25.1 (A), U10.28 (GPB3)
~STM32L496_RST: C18.1, J9.5, JP30.2 (B), R6.2, U3.25 (NRST)
~Tastatur_RST: C20.1, J10.5, R7.2, U8.14 (~RESET), U10.1 (GPB4), U13.7 (NRST)

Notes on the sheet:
Speicher
VDDIO2
DEBUG
VDD
RS232
2N7002NXBK
BLUENRG-M2SP
MCP23017
VDDA
VDDUSB

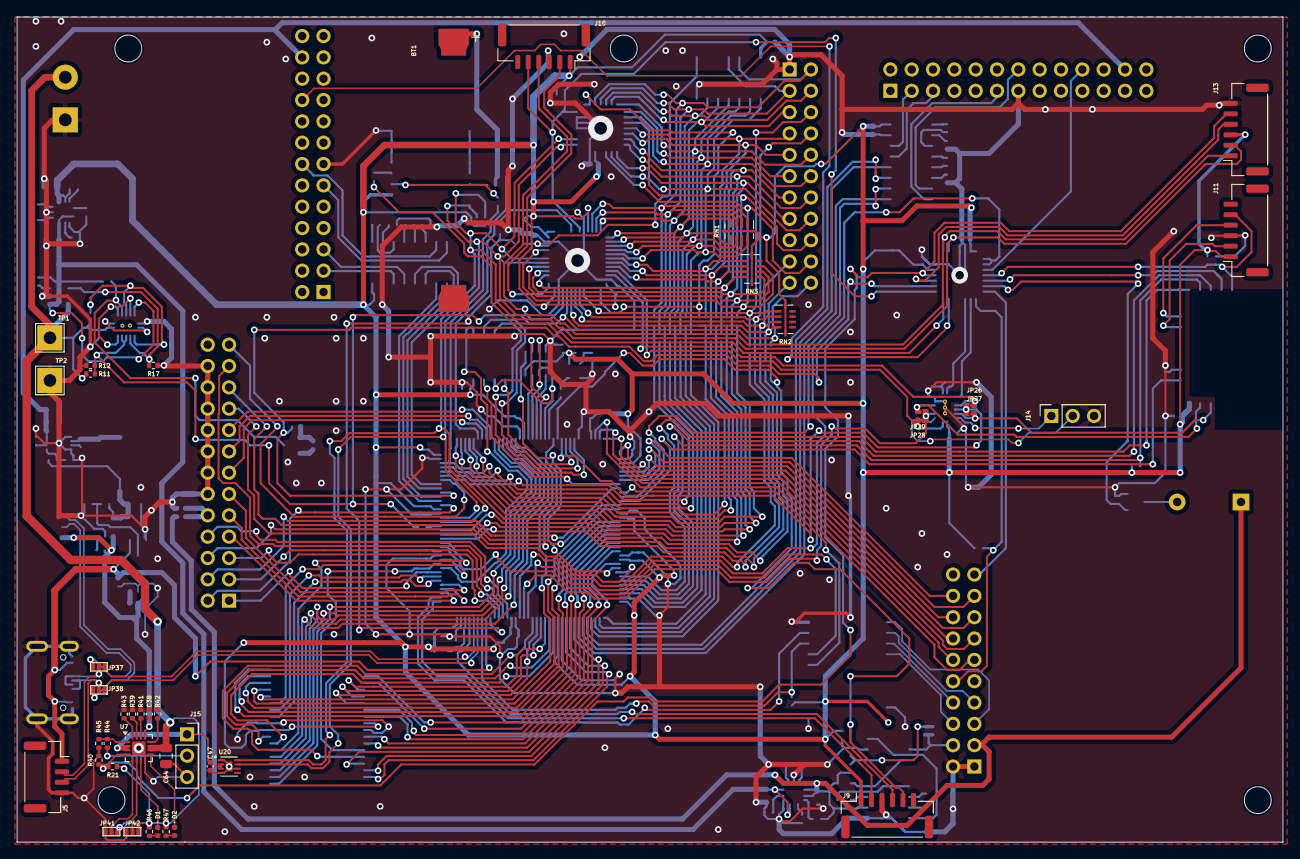
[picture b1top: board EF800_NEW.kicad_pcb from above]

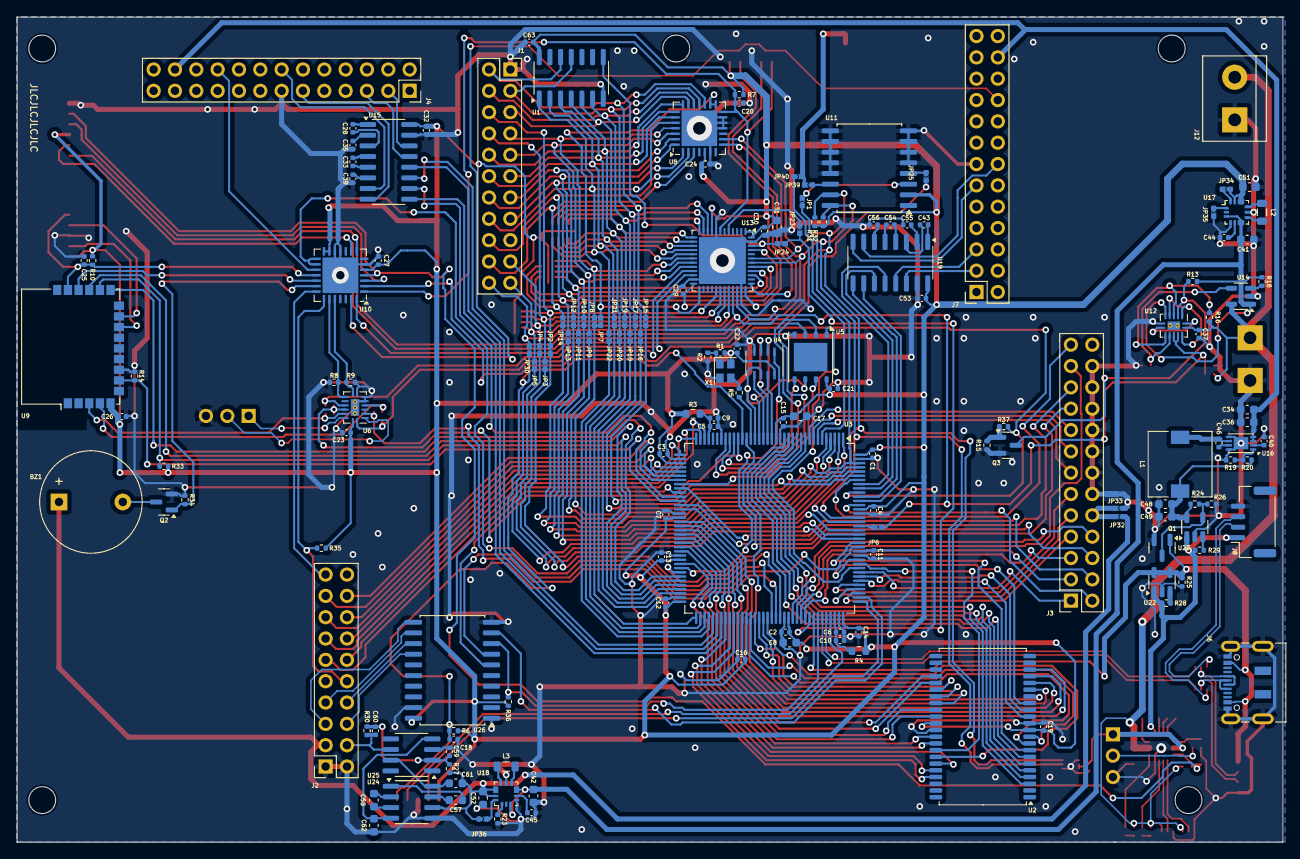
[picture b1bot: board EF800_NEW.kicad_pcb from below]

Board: 2 copper layers, 150.8 x 98.2 mm, 205 parts (164 on the bottom side), 254 nets.
